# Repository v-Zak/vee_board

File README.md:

# ErgoBoard

A personalised keyboard clone of a [Josukey](https://github.com/Narkoleptika/josukey) which is based off a corne. This version is Diodless and Wireless only.

The board was created using the below method.

# Initial Layout

## [ErgoPad](https://github.com/pashutk/ergopad)
Use Ergopad to get a rough layout of one of the halves using a tablet.

## [Ergogen](https://github.com/ergogen/ergogen)
Use Ergogen to recreate the layout using the online tool first for the live viewer.

# [Josukey Fork](https://github.com/Narkoleptika/josukey)
Use Josukey NPM as it includes the footprints for the nano etc. Follow the installation instructions below.

## Prerequisites
* Node
* Docker
* Kicad
  
## Getting Started

### Installation

Get my files on your computer and install dependencies.

```bash
git clone https://github.com/v-Zak/ergoboard.git
cd ergoboard
npm i
```

## Ergogen

### Build

This will run Ergogen and build all of the output files. 
https
```bash
npm run ergogen:build
```

This will overwrite the output folder so once happy with the pcb move to kicad folder before routing.

### Watch

This will watch the `config.yaml` file and the `footprints` directory and run the build command whenever there are changes.

```bash
npm run ergogen:watch
```

Same story so move to kicad folder

## Routing

Route all the nets within kicad and then export to a gerber file refer to [this video](https://youtu.be/M_VuXVErD6E?si=WyvUVawYogwmqlh6) for help

Use plot to create gerber files, once routed and then order off a pcb website by uploading the gerber.zip

## Order Parts 

The parts list (for the v_zak keyboard) needed is as follows:

| Name                                 | Quantity | Link                                                                                                                       | Cost ($) |
|--------------------------------------|----------|----------------------------------------------------------------------------------------------------------------------------|----------|
| PCB (Use Gerber)                     | 2        | JLPCB or PCBWay                                                                                                            | 12.93    |
| JST 2.0 PH Female                    | 2        | [aliexpress](https://www.aliexpress.com/item/33009614944.html?spm=a2g0o.order_list.order_list_main.5.761818026oXKZu)       | 1.70     |
| 3x6 Micro Switch                     | 2        | [aliexpress](https://www.aliexpress.com/item/4000700060759.html?spm=a2g0o.order_list.order_list_main.11.761818026oXKZu)    | 2.96     |
| 7 pin 3mm & 1.5mm gap Slide Switch   | 2        | [aliexpress](https://www.aliexpress.com/item/1005003829889015.html?spm=a2g0o.order_list.order_list_main.16.761818026oXKZu) | 2.82     |
| ProMicro NRF52840 (Nice! Nano Clone) | 2        | [aliexpress](https://www.aliexpress.com/item/1005006074191337.html?spm=a2g0o.order_list.order_list_main.28.761818026oXKZu) | 16.74    |
| 1u Choc PBT Keycaps                  | 36       | [aliexpress](https://www.aliexpress.com/item/1005004558099208.html?spm=a2g0o.order_list.order_list_main.33.761818026oXKZu) | 27.00    |
| Kalih Choc Red Keycaps               | 36       | [aliexpress](https://www.aliexpress.com/item/1005005066585322.html?spm=a2g0o.order_list.order_list_main.21.761818026oXKZu) | 20.00    |

The total as of 11/11/23 is: 84

## Build guide

refer to [corne](https://github.com/foostan/crkbd) build guides and ignore the diodes. 

## ZMK

refer to [zmk-config repo](https://github.com/v-Zak/zmk-config).

Automatically builds the .uf2 files for flashing using the configs in the config folder.

To change the hardware / board pinouts go into the shields folder and change the files to suit gpio pins etc.

To change keymap and software settings just use the .conf and .keymap files in the config folder.

## Flash 

Drop the uf2 files found in the actions section in github into the folder that appears when the keyboard is connected to the computer. Make sure the left is flashed to the left and the right to the right.

Now test it out!

## Thanks
* <a href="https://github.com/Narkoleptika/josukey" target="_blank">Josukey</a>
* <a href="https://github.com/benvallack/ergogen" target="_blank">BenVallack</a>
* <a href="https://github.com/ergogen/ergogen" target="_blank">Ergogen</a>
* <a href="https://discord.gg/nbKcAZB" target="_blank">Absolem Club Discord</a>
* <a href="https://github.com/tsteffek/Ergogen-V4-Migration-Guide" target="_blank">V4 Migration Guide</a>
* <a href="https://gitlab.com/Audijo/keyboard" target="_blank">Claw</a>
* <a href="https://github.com/MrCarney/mrkeyboard" target="_blank">MrKeyboard</a>
* <a href="https://github.com/foostan/crkbd" target="_blank">Corne keyboard</a>
* <a href="https://github.com/zmkfirmware/zmk" target="_blank">ZMK</a>
* <a href="https://github.com/manna-harbour/miryoku_zmk" target="_blank">Miryoku ZMK</a>

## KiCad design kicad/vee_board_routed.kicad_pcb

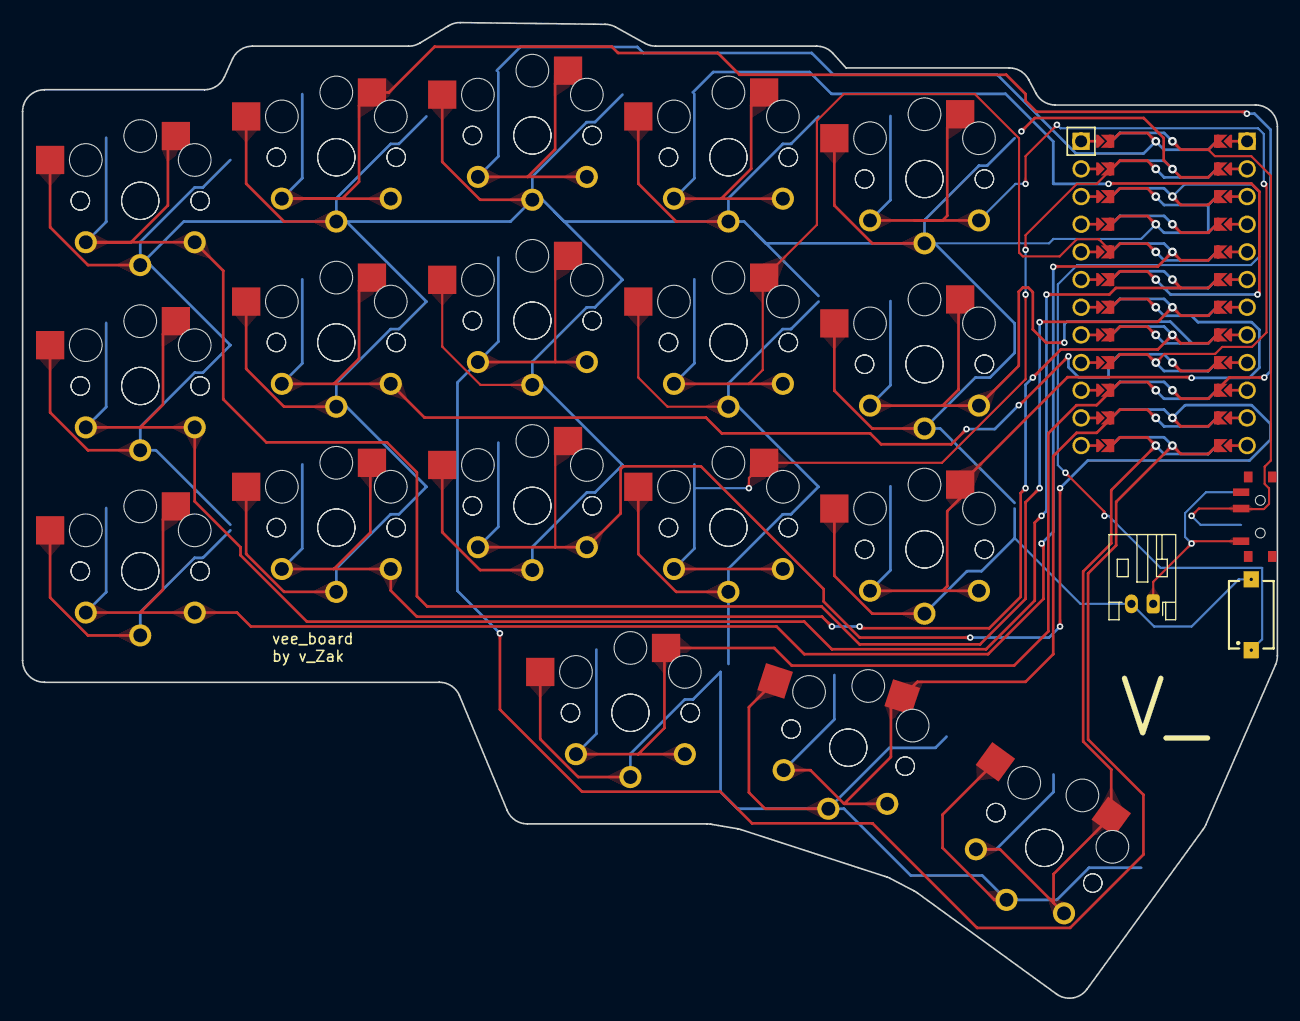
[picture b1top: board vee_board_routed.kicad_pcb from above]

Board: 2 copper layers, 115.2 x 89.6 mm, 40 parts (0 on the bottom side), 22 nets.

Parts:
MCU1: ProMicro
S1, S2, S3, S4, S5, S6, S7, S8, S9, S10, S11, S12, S13, S14, S15, S16, S17, S18, S19, S20, S21, S22, S23, S24, S25, S26, S27, S28, S29, S30, S31, S32, S33, S34, S35, S36: PG1350
S37: 434121025816
T1: SW_SPDT_PCM12
_1: JST_PH_S2B-PH-K_1x02_P2.00mm_Horizontal

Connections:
GND: MCU1.2, MCU1.21, MCU1.22, S1.2, S2.2, S3.2, S4.2, S5.2, S6.2, S7.2, S8.2, S9.2, S10.2, S11.2, S12.2, S13.2, S14.2, S15.2, S16.2, S17.2, S18.2, S19.2, S20.2, S21.2, S22.2, S23.2, S24.2, S25.2, S26.2, S27.2, S28.2, S29.2, S30.2, S31.2, S32.2, S33.2, S34.2, S35.2, S36.2, S37.2, _1.2
P0: MCU1.23, S10.1, S28.1
P1: MCU1.24, S9.1, S27.1
P2: MCU1.20, S11.1, S29.1
P3: MCU1.19, S12.1, S30.1
P4: MCU1.18, S13.1, S31.1
P5: MCU1.17, S14.1, S32.1
P6: MCU1.16, S15.1, S33.1
P7: MCU1.15, S16.1, S34.1
P8: MCU1.14, S17.1, S35.1
P9: MCU1.13, S18.1, S36.1
P10: MCU1.12, S8.1, S26.1
P14: MCU1.10, S6.1, S24.1
P15: MCU1.9, S5.1, S23.1
P16: MCU1.11, S7.1, S25.1
P18: MCU1.8, S4.1, S22.1
P19: MCU1.7, S3.1, S21.1
P20: MCU1.6, S2.1, S20.1
P21: MCU1.5, S1.1, S19.1
RAW: MCU1.1, T1.2
RST: MCU1.3, S37.1
pos: T1.1, _1.1
